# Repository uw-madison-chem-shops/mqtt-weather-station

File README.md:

# MQTT weather station

Simple station for monitoring environmental conditions in the lab over MQTT.

Based on the Bosch's [BME280 humidity, pressure, and temperature sensor](https://www.bosch-sensortec.com/products/environmental-sensors/humidity-sensors-bme280/).
Using Adafruit's [breakout board](https://www.adafruit.com/product/2652).

Designed to work with [mqtt.chem.wisc.edu](https://mqtt.chem.wisc.edu/).

## Repository

This is an open source hardware project licensed under the CERN Open Hardware Licence Version 2 - Permissive.
Please see the LICENSE file for the complete license.

This repository is being mirrored to several version control systems in an attempt to ensure maximum avaliability.

| name             | url                                                                           |
| ---------------- | ----------------------------------------------------------------------------- |
| blaise           | https://git.blaise.zone/uw-madison-chem-shops/mqtt-weather-station.git/about/ |
| Codeberg         | https://codeberg.org/uw-madison-chem-shops/mqtt-weather-station               |
| GitHub (primary) | https://github.com/uw-madison-chem-shops/mqtt-weather-station                 |
| GitLab           | https://gitlab.com/uw-madison-chem-shops/mqtt-weather-station                 |

## PCB

This PCB was designed using KiCAD version 5.
Refer to `weather.pdf` for schematic.
PCB images generated with [tracespace](https://github.com/tracespace/tracespace) follow.

## Bill of Materials

| reference      | value            | manufacturer     | part number          | price  | vendors |
| :------------- | :--------------- | :--------------- | :------------------- | :----- | :------ |
| A1             | ESP8266 breakout | Adafruit         | 2471                 | $10.00 | [Adafruit](https://www.adafruit.com/product/2471) [DigiKey](https://www.digikey.com/en/products/detail/adafruit-industries-llc/2471/5355489) |
| C1             | 100u             | Illinois Cap.    | 107KXM025M           | $0.25  | [DigiKey](https://www.digikey.com/en/products/detail/illinois-capacitor/107KXM025M/5410757?s=N4IgTCBcDaIIwAYDsBpAGgWQWArBkAugL5A) |
| C2             | 10u              | Yageo            | CC1206KKX7R8BB106    | $0.25  | [DigiKey](https://www.digikey.com/en/products/detail/yageo/CC1206KKX7R8BB106/5195365?s=N4IgTCBcDaIMJwIxgAwDYDSGAaB2ASgBwBCxi6IAugL5A) |
| C3             | 22u              | Yageo            | CC1206MKX7R7BB226    | $0.75  | [DigiKey](https://www.digikey.com/en/products/detail/yageo/CC1206MKX7R7BB226/7071713?s=N4IgTCBcDaIMJwIxgAwDYCyBpAGgdgCU8AhYsMNEAXQF8g) |
| C4, C5         | 1u               |                  |                      |        |         |
| D1, D2         | red LED          | Lite-ON          | LTST-C230KRKT        | $0.50  | [DigiKey](https://www.digikey.com/en/products/detail/lite-on-inc/LTST-C230KRKT/386857?s=N4IgTCBcDaIDIBUDKCC0BhMBmADAaQCU8EQBdAXyA) |
| J1             | barrel jack      |                  |                      | $1.00  | |
| PS1            | VXO7805-500-M    |                  |                      | $3.00  | |
| Q1, Q2         | MOSFET N-ENH     | Diodes Inc.      | 2N7002K-7            | $0.25  | [DigiKey](https://www.digikey.com/en/products/detail/diodes-incorporated/2N7002K-7/1934378?lang=en&s=N4IgTCBcDa4HIHYAMSwGkC0CQF0C%2BQA&site=us&x=17&y=13) [Mouser](https://www.mouser.com/ProductDetail/Diodes-Incorporated/2N7002K-7?qs=rGAXPo9uwV0%2Fp9r5KJ7huA%3D%3D) |
| R1, R2         | 1k               |
| R3, R4, R7, R8 | 4.7k             |
| R5             | 470k             |
| R6, R9         | 1M               |
| U1             | BME280 breakout  | Adafruit         | 2652                 | $20.00 | [Adafruit](https://www.adafruit.com/product/2652) [DigiKey]() |
| U2             | counter          | TI               | CD4060BM96           | $0.50  |

All prices are extended.
Assuming an order of 10 PCBs, the boards themselves should cost around $5 each.

## Firmware

This project uses [micropython](https://micropython.org/), specifically [microhomie](https://github.com/microhomie/microhomie).
Refer to the "firmware" directory in this repository for detailed instructions.

## Changelog

#### Fixed
- value of C5

### Unprinted

### B

#### Added
- new hour long reset timer based on CD4060BM96

#### Changed
- SOT23 packages for all discrete transistors

### A

#### Added
- initial design

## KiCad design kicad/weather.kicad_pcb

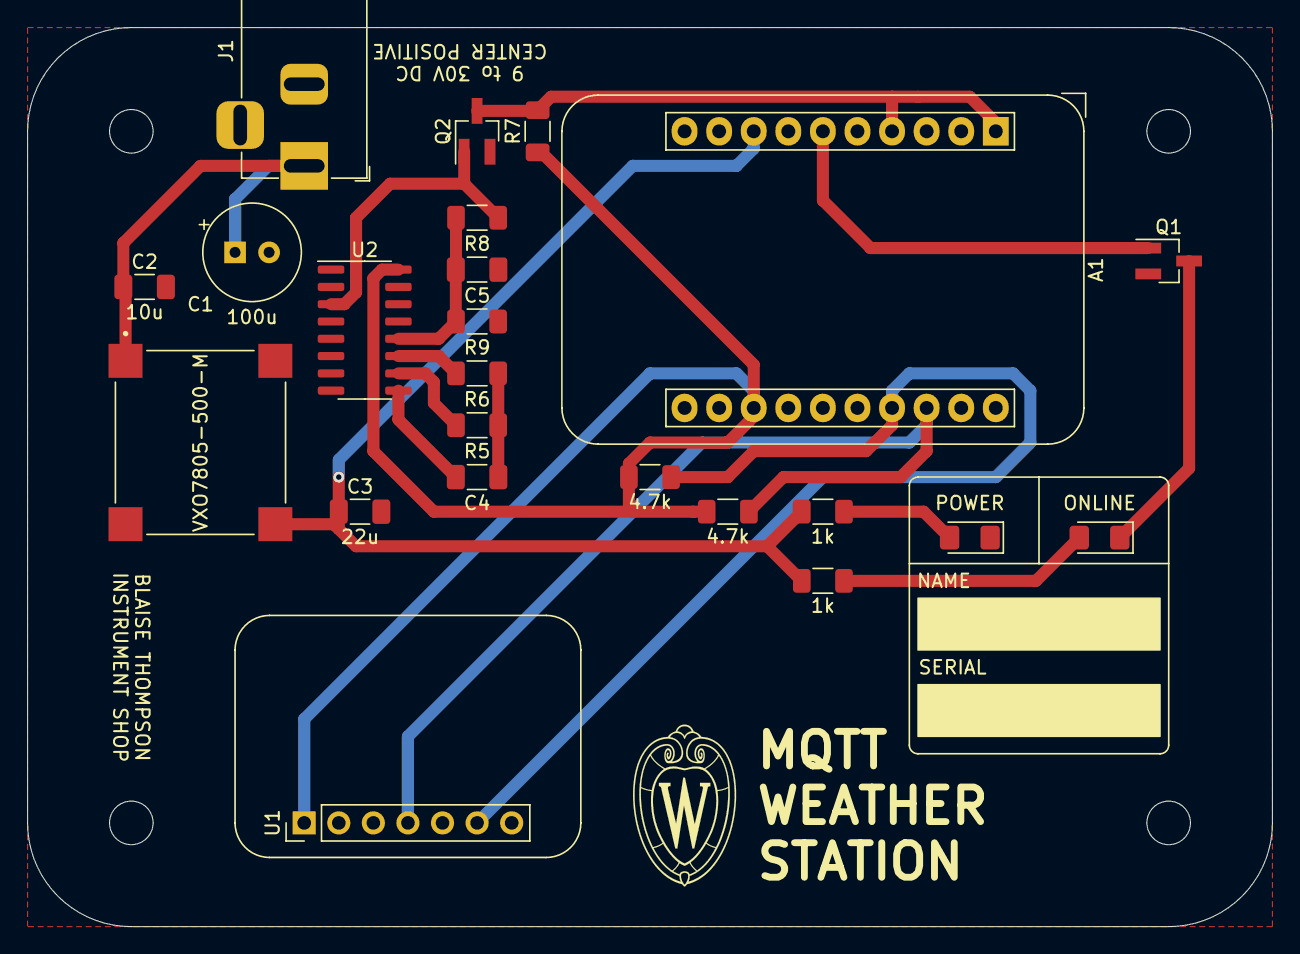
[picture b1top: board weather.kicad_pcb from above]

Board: 2 copper layers, 91.4 x 66.0 mm, 23 parts (0 on the bottom side), 17 nets.

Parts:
A1: Adafruit_HUZZAH_ESP8266_breakout
C1: 100u; CP_Radial_Tantal_D7.0mm_P2.50mm
C2: 10u; C_1206_3216Metric_Pad1.33x1.80mm_HandSolder
C3: 22u; C_1206_3216Metric_Pad1.33x1.80mm_HandSolder
C4: 1n; C_1206_3216Metric_Pad1.33x1.80mm_HandSolder
C5: C; C_1206_3216Metric_Pad1.33x1.80mm_HandSolder
D1, D2: LED; LED_1206_3216Metric_Pad1.42x1.75mm_HandSolder
J1: Barrel_Jack; BarrelJack_Horizontal
PS1: VXO7805-500-M; CONV_VXO7805-500-M
Q1, Q2: 2N7000; SOT-23_Handsoldering
R1, R2: 1k; R_1206_3216Metric_Pad1.30x1.75mm_HandSolder
R3, R4: 4.7k; R_1206_3216Metric_Pad1.30x1.75mm_HandSolder
R5: 100k; R_1206_3216Metric_Pad1.30x1.75mm_HandSolder
R6: 1M; R_1206_3216Metric_Pad1.30x1.75mm_HandSolder
R7, R8, R9: R_US; R_1206_3216Metric_Pad1.30x1.75mm_HandSolder
U1: BME280; PinHeader_1x07_P2.54mm_Vertical
U2: CD4060BM96; SOIC-16_3.9x9.9mm_P1.27mm

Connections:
+3V3: A1.13, R3.1, R4.1, R7.1, U1.1, U2.16
+5V: A1.8, C3.1, PS1.3, R1.1, R2.1
GND: A1.10, A1.11, C1.2, C2.2, C3.2, C5.2, D1.1, J1.2, PS1.2, Q1.2, Q2.2, R9.2, U1.3, U2.8
unnamed: A1.1, A1.4, Q2.3, R7.2
unnamed: A1.6, Q1.1
unnamed: A1.17, R4.2, U1.6
unnamed: A1.18, R3.2, U1.4
unnamed: C1.1, C2.1, J1.1, PS1.1
unnamed: C4.1, U2.9
unnamed: C4.2, R5.1, R6.1
unnamed: C5.1, R8.2, R9.1, U2.12
unnamed: D1.2, R1.2
unnamed: D2.1, Q1.3
unnamed: D2.2, R2.2
unnamed: Q2.1, R8.1, U2.3
unnamed: R5.2, U2.10
unnamed: R6.2, U2.11

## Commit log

2021-03-08 remove microhomie subrepo
2021-03-08 gitignore false
2021-03-09 firmware version 1
2021-03-09 firmware readme
2021-03-09 forgotten add
2021-03-09 readme formatting
2021-04-05 bme280
2021-04-06 license
2021-04-06 organize repository
2021-04-07 4060
2021-04-13 revisionB
2021-04-13 2n7000-sot23
2021-05-25 after building one
2021-06-30 add ip to nodes
2021-06-30 return bme680
2021-07-30 warm-up measurements
2021-08-04 add blaise, codeberg as remotes
2023-03-15 slightly bigger holes adapter plate
2023-10-25 C5 1u BOM
